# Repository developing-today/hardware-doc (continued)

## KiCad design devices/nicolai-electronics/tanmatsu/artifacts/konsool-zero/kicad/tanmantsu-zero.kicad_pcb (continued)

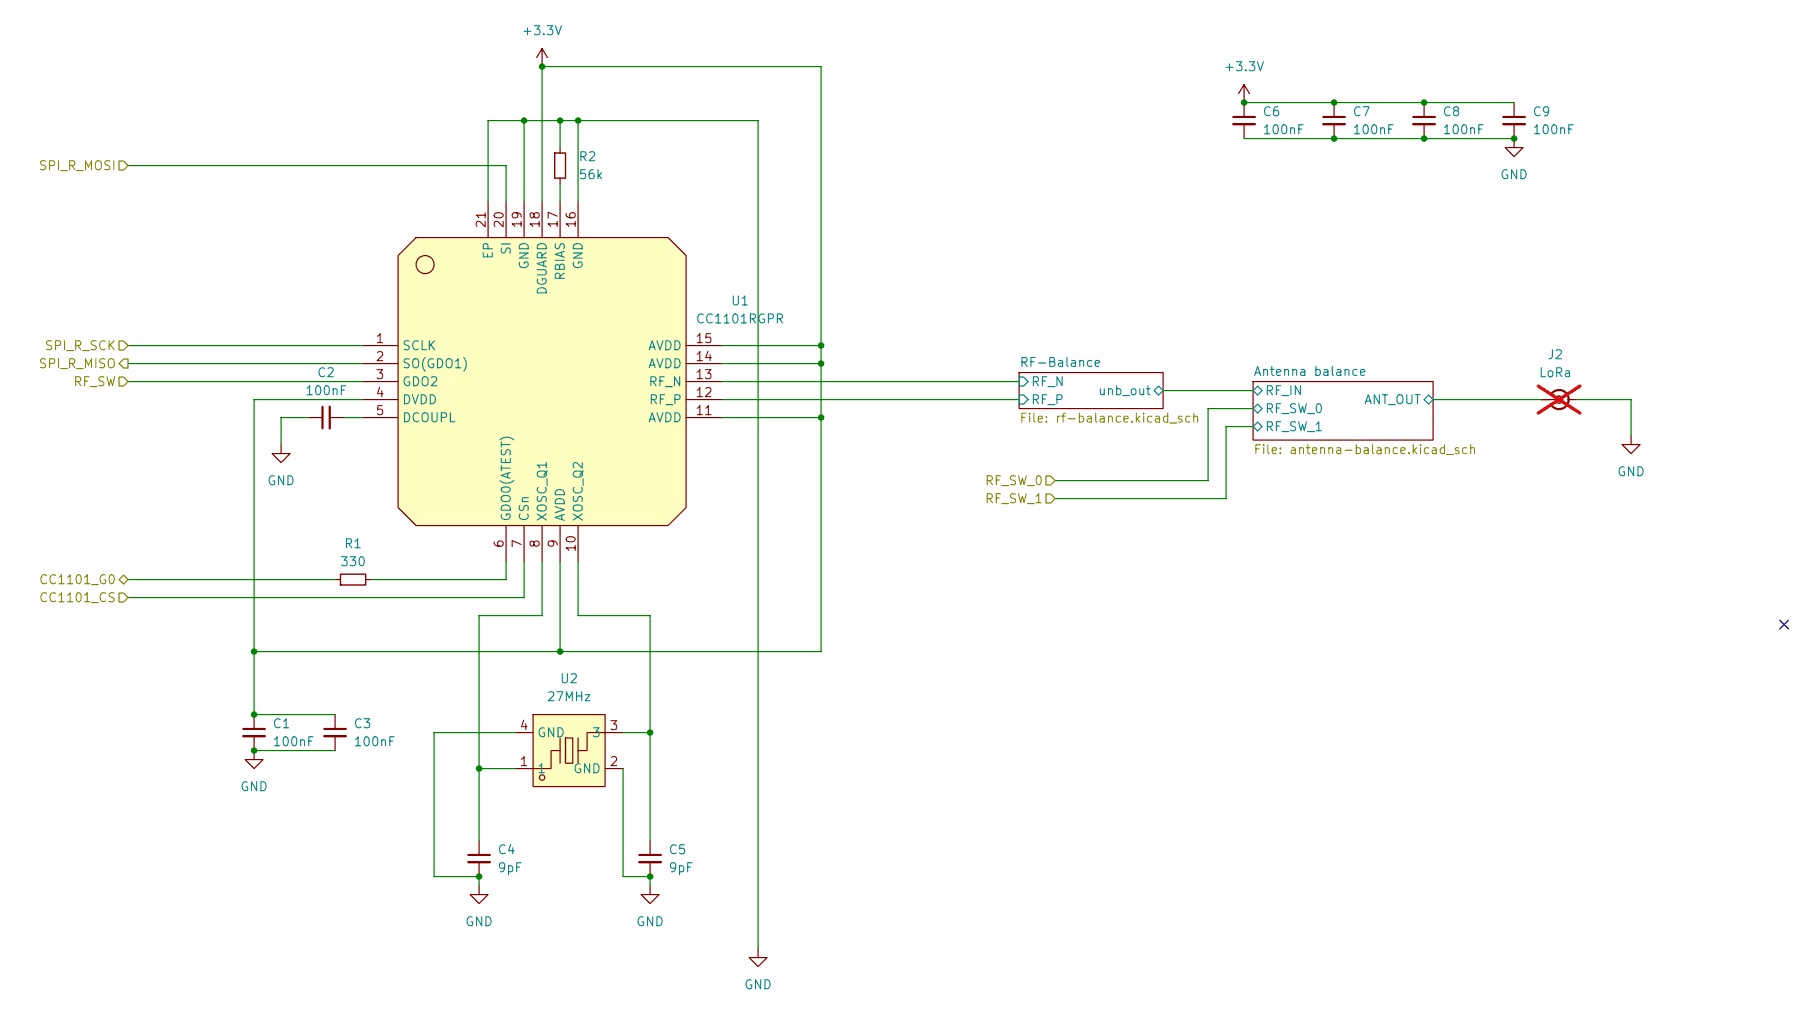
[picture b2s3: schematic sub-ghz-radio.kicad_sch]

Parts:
C1, C2, C3, C6, C7, C8, C9: 100nF; C_0402_1005Metric; LCSC C5448844
C4, C5: 9pF; C_0402_1005Metric; LCSC C426043
J2: LoRa; SMA_Samtec_SMA-J-P-H-ST-EM1_EdgeMount; not fitted
R1: 330; R_0402_1005Metric; LCSC C25104
R2: 56k; R_0402_1005Metric; LCSC C203188
U1: CC1101RGPR; QFN-20_L4.0-W4.0-P0.5-TL-EP; LCSC Part C29953
U2: 27MHz; OSC-SMD_4P-L3.2-W2.5-BL; LCSC Part C555573

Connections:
+3.3V: C1.1, C3.1, C6.1, C7.1, C8.1, C9.1, U1.4 (DVDD), U1.9 (AVDD), U1.11 (AVDD), U1.14 (AVDD), U1.15 (AVDD), U1.18 (DGUARD); also elsewhere on the board
/sub-GHz-radio/Antenna balance/ANT_OUT: J2.1 (In); also elsewhere on the board
/sub-GHz-radio/RF-Balance/RF_N: U1.13 (RF_N); also elsewhere on the board
/sub-GHz-radio/RF-Balance/RF_P: U1.12 (RF_P); also elsewhere on the board
E0: U1.3 (GDO2); also elsewhere on the board
E1: R1.1; also elsewhere on the board
GND: C1.2, C2.1, C3.2, C4.2, C5.2, C6.2, C7.2, C8.2, C9.2, J2.2 (Ext), R2.1, U1.16 (GND), U1.19 (GND), U1.21 (EP), U2.2 (GND), U2.4 (GND); also elsewhere on the board
unnamed: C2.2, U1.5 (DCOUPL)
unnamed: R1.2, U1.6 (GDO0(ATEST))
unnamed: R2.2, U1.17 (RBIAS)
unnamed: C4.1, U1.8 (XOSC_Q1), U2.1
unnamed: C5.1, U1.10 (XOSC_Q2), U2.3
SPI_CMD: U1.20 (SI); also elsewhere on the board
SPI_D0: U1.2 (SO(GDO1)); also elsewhere on the board
SPI_D3: U1.7 (CSn); also elsewhere on the board
SPI_SCK: U1.1 (SCLK); also elsewhere on the board

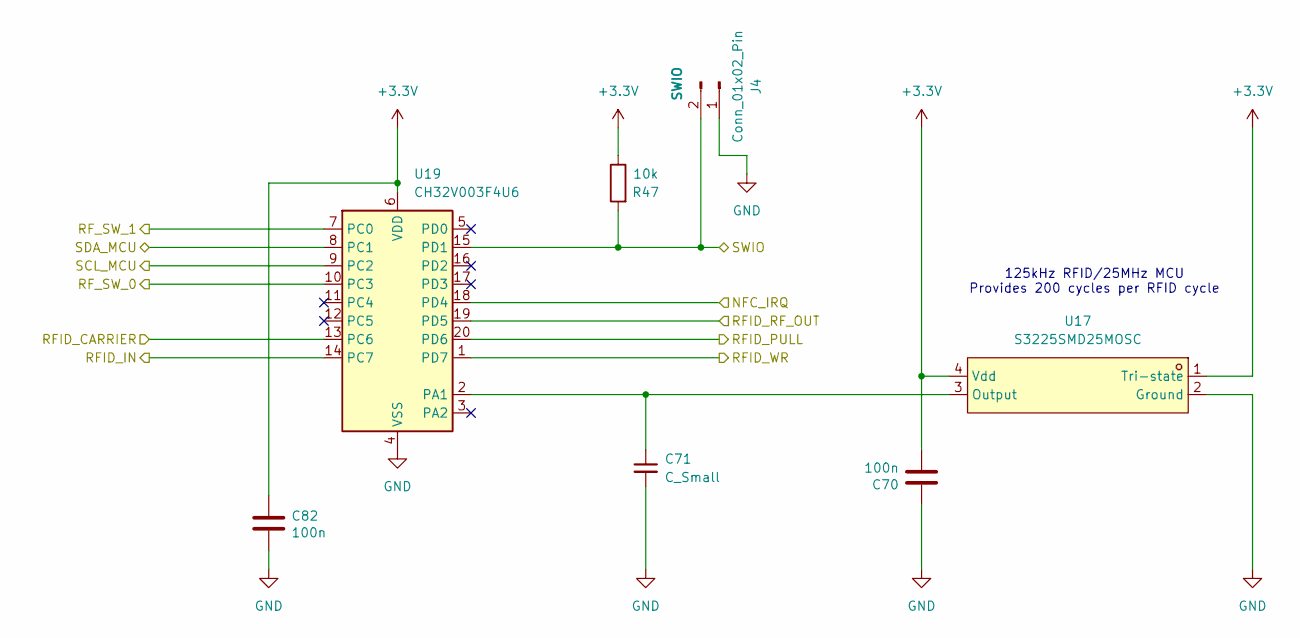
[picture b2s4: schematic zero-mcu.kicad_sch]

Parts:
C70, C82: 100n; C_0402_1005Metric; LCSC C307331
C71: C_Small; C_0402_1005Metric; LCSC C1548
J4: Conn_01x02_Pin; PinHeader_1x02_P2.54mm_Vertical
R47: 10k; R_0402_1005Metric; LCSC C60490
U17: S3225SMD25MOSC; OSC-SMD_4P-L3.2-W2.5-BL; LCSC Part C7431183
U19: CH32V003F4U6; QFN-20-1EP_3x3mm_P0.4mm_EP1.65x1.65mm

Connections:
+3.3V: C70.2, C82.1, R47.1, U17.1 (Tri-state), U17.4 (Vdd), U19.6 (VDD); also elsewhere on the board
E4: J4.2, R47.2, U19.15 (PD1); also elsewhere on the board
GND: C70.1, C71.2, C82.2, J4.1, U17.2 (Ground), U19.4 (VSS), U19.21 (VSS); also elsewhere on the board
INT_SCL: U19.9 (PC2); also elsewhere on the board
INT_SDA: U19.8 (PC1); also elsewhere on the board
NFC_IRQ: U19.18 (PD4); also elsewhere on the board
unnamed: C71.1, U17.3 (Output), U19.2 (PA1)
RFID_CARRIER: U19.13 (PC6); also elsewhere on the board
RFID_IN: U19.14 (PC7); also elsewhere on the board
RFID_PULL: U19.20 (PD6); also elsewhere on the board
RFID_RF_OUT: U19.19 (PD5); also elsewhere on the board
RFID_WR_IN: U19.1 (PD7); also elsewhere on the board
RF_SW_0: U19.10 (PC3); also elsewhere on the board
RF_SW_1: U19.7 (PC0); also elsewhere on the board

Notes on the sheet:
125kHz RFID/25MHz MCU Provides 200 cycles per RFID cycle

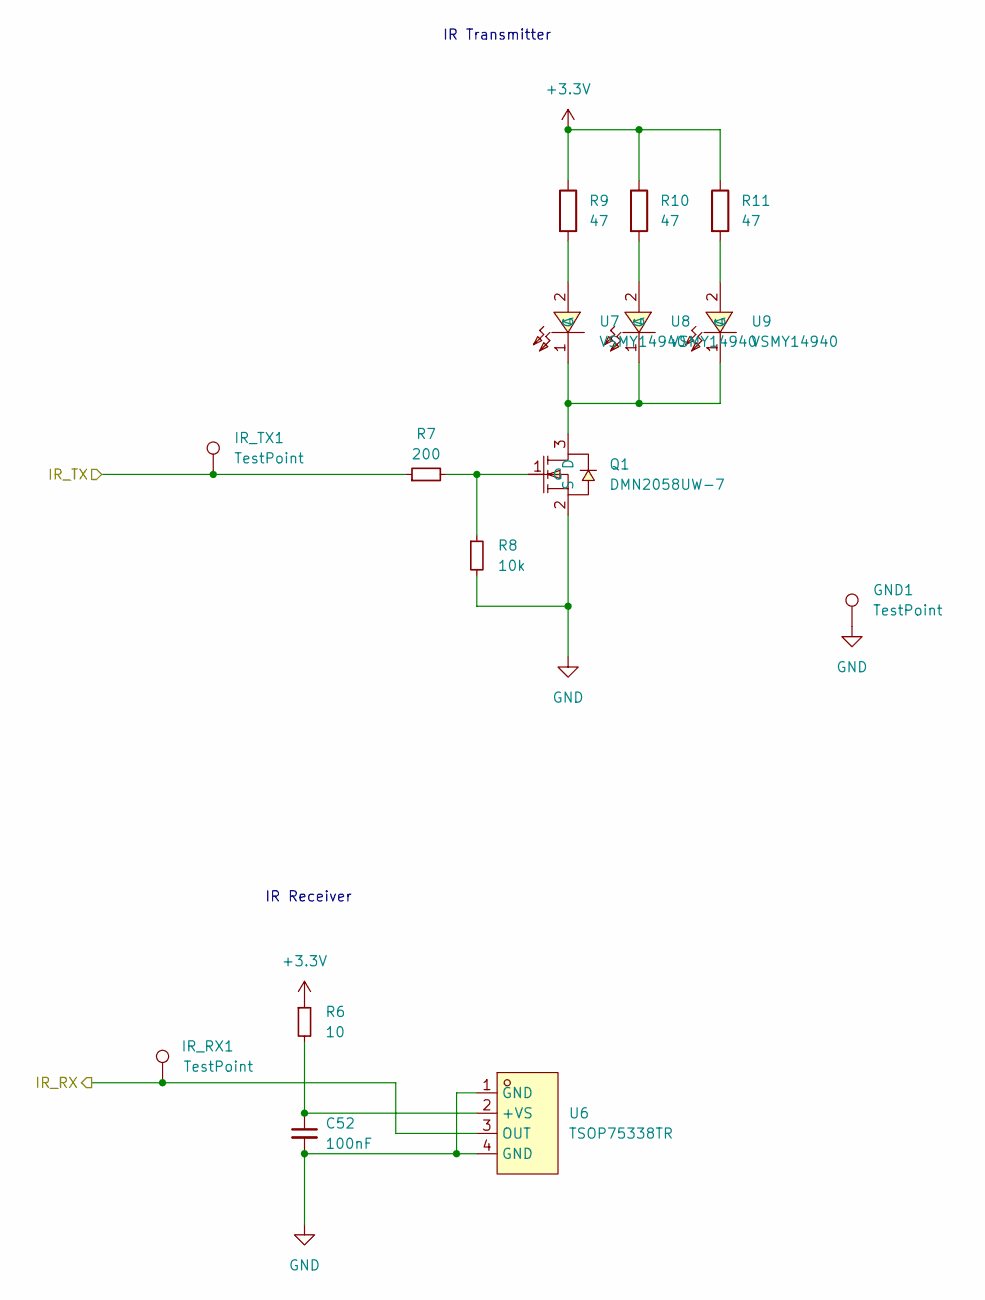
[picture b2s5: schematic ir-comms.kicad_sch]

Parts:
C52: 100nF; C_0402_1005Metric; LCSC C5448844
GND1: TestPoint; TestPoint_Pad_D1.0mm
IR_RX1: TestPoint; TestPoint_Pad_D1.0mm
IR_TX1: TestPoint; TestPoint_Pad_D1.0mm
Q1: DMN2058UW-7; SOT-323-3_L2.2-W1.3-P1.30-LS2.1-BR; LCSC Part C2760648
R6: 10; R_0402_1005Metric
R7: 200; R_0402_1005Metric; LCSC C25087
R8: 10k; R_0402_1005Metric; LCSC C25744
R9, R10, R11: 47; R_0805_2012Metric; LCSC C17714
U6: TSOP75338TR; SENSOR-SMD_TSOP75238TR; LCSC Part C6561231
U7, U8, U9: VSMY14940; LED-SMD_VSMY14940; LCSC Part C511069

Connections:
+3.3V: R6.1, R9.1, R10.1, R11.1; also elsewhere on the board
E9: IR_RX1.1, U6.3 (OUT); also elsewhere on the board
E10: IR_TX1.1, R7.1; also elsewhere on the board
GND: C52.2, GND1.1, Q1.2 (S), R8.2, U6.1 (GND), U6.4 (GND); also elsewhere on the board
unnamed: Q1.3 (D), U7.1 (C), U8.1 (C), U9.1 (C)
unnamed: Q1.1 (G), R7.2, R8.1
unnamed: C52.1, R6.2, U6.2 (+VS)
unnamed: R9.2, U7.2 (A)
unnamed: R10.2, U8.2 (A)
unnamed: R11.2, U9.2 (A)

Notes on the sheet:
IR Receiver
IR Transmitter

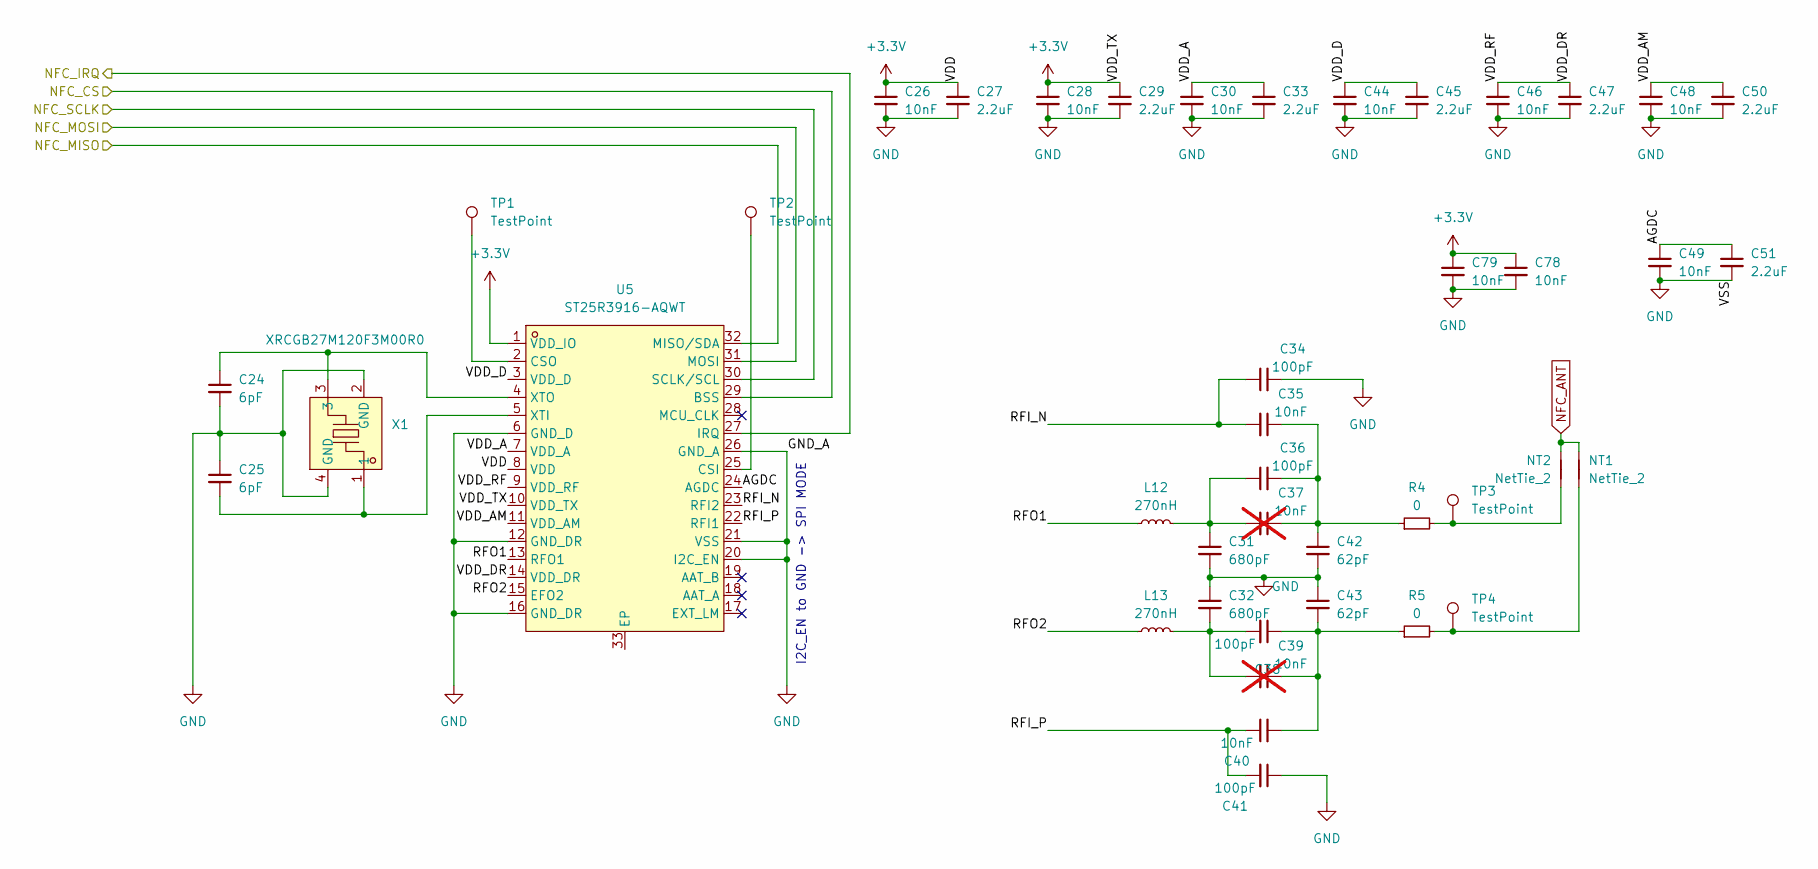
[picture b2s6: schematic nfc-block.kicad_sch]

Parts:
C24, C25: 6pF; C_0402_1005Metric; LCSC C1575
C26, C28, C30, C35, C40, C44, C46, C48, C49, C78, C79: 10nF; C_0402_1005Metric; LCSC C15195
C27, C29, C33, C45, C47, C50, C51: 2.2uF; C_0603_1608Metric; LCSC C23630
C31, C32: 680pF; C_0402_1005Metric; LCSC C295936
C34, C36, C38, C41: 100pF; C_0402_1005Metric; LCSC C1523
C37, C39: 10nF; C_0402_1005Metric; LCSC C15195; not fitted
C42, C43: 62pF; L_0402_1005Metric; LCSC C3887028
L12, L13: 270nH; L_0402_1005Metric; LCSC C76784
NT1, NT2: NetTie_2; NetTie-2_SMD_Pad0.5mm
R4, R5: 0; R_0402_1005Metric; LCSC C17168
TP1, TP2: TestPoint; TestPoint_Pad_1.0x1.0mm
TP3, TP4: TestPoint; TestPoint_Pad_D1.0mm
U5: ST25R3916-AQWT; VFQFPN-32_L5.0-W5.0-P0.50-TL-EP3.5; LCSC Part C2908147
X1: XRCGB27M120F3M00R0; CRYSTAL-SMD_4P-L2.0-W1.6-BL-B; LCSC Part C576558

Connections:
+3.3V: C26.1, C27.1, C28.1, C29.1, C78.1, C79.1, U5.1 (VDD_IO), U5.8 (VDD), U5.10 (VDD_TX); also elsewhere on the board
/NFC block/AGDC: C49.1, C51.1, U5.24 (AGDC)
/NFC block/RFI_N: C34.1, C35.2, U5.23 (RFI2)
/NFC block/RFI_P: C40.1, C41.2, U5.22 (RFI1)
/NFC block/RFO1: L12.1, U5.13 (RFO1)
/NFC block/RFO2: L13.1, U5.15 (EFO2)
/NFC block/VDD_A: C30.1, C33.1, U5.7 (VDD_A)
/NFC block/VDD_AM: C48.1, C50.1, U5.11 (VDD_AM)
/NFC block/VDD_D: C44.1, C45.1, U5.3 (VDD_D)
/NFC block/VDD_DR: C46.1, C47.1, U5.9 (VDD_RF), U5.14 (VDD_DR)
E3: U5.29 (BSS); also elsewhere on the board
GND: C24.2, C25.1, C26.2, C27.2, C28.2, C29.2, C30.2, C31.2, C32.1, C33.2, C34.2, C41.1, C42.2, C43.1, C44.2, C45.2, C46.2, C47.2, C48.2, C49.2, C50.2, C51.2, C78.2, C79.2, U5.6 (GND_D), U5.12 (GND_DR), U5.16 (GND_DR), U5.20 (I2C_EN), U5.21 (VSS), U5.26 (GND_A), X1.2 (GND), X1.4 (GND); also elsewhere on the board
NFC_ANT: NT1.2, NT2.1
NFC_IRQ: U5.27 (IRQ); also elsewhere on the board
unnamed: C31.1, C36.1, C37.2, L12.2
unnamed: C32.2, C38.2, C39.2, L13.2
unnamed: C35.1, C36.2, C37.1, C42.1, R4.1
unnamed: C38.1, C39.1, C40.2, C43.2, R5.1
unnamed: NT1.1, R5.2, TP4.1
unnamed: NT2.2, R4.2, TP3.1
unnamed: TP2.1, U5.25 (CSI)
unnamed: TP1.1, U5.2 (CSO)
unnamed: C25.2, U5.5 (XTI), X1.1
unnamed: C24.1, U5.4 (XTO), X1.3
SPI_CMD: U5.31 (MOSI); also elsewhere on the board
SPI_D0: U5.32 (MISO/SDA); also elsewhere on the board
SPI_SCK: U5.30 (SCLK/SCL); also elsewhere on the board

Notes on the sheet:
I2C_EN to GND -> SPI MODE

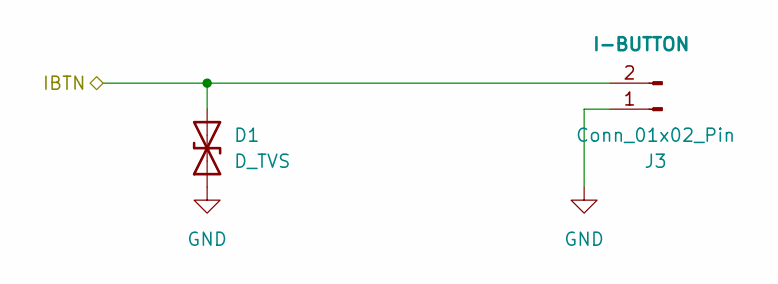
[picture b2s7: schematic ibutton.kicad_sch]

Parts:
D1: D_TVS; D_0402_1005Metric; LCSC C19626254
J3: Conn_01x02_Pin; PinHeader_1x02_P2.54mm_Vertical

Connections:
GND: D1.1 (A1), J3.1; also elsewhere on the board
IBTN: D1.2 (A2), J3.2

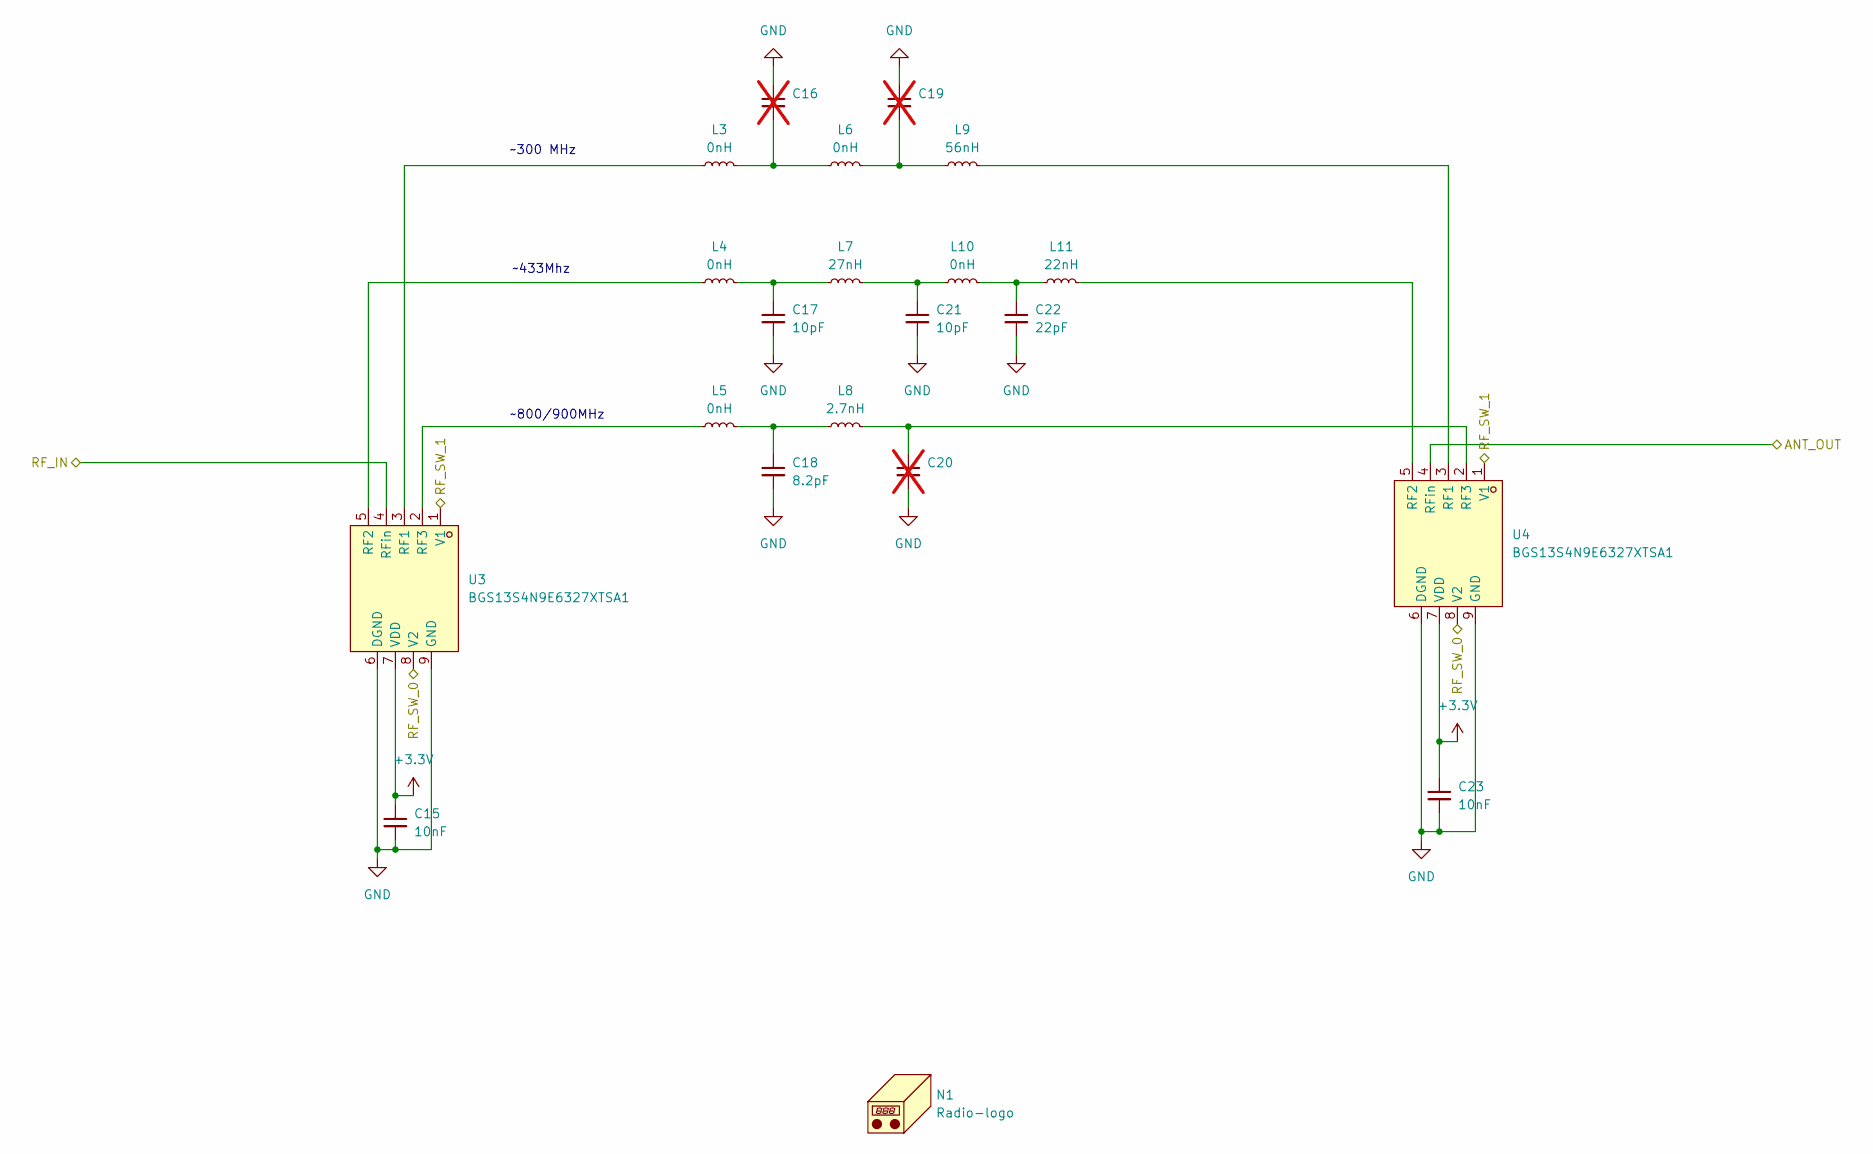
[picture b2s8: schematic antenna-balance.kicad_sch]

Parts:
C15, C23: 10nF; C_0402_1005Metric; LCSC C15195
C16, C19, C20: C_0402_1005Metric; LCSC C32949; not fitted
C17, C21: 10pF; C_0402_1005Metric; LCSC C32949
C18: 8.2pF; C_0402_1005Metric; LCSC C76984
C22: 22pF; C_0402_1005Metric; LCSC C1555
L3, L4, L5, L6, L10: 0nH; L_0402_1005Metric; LCSC C17168
L7: 27nH; L_0402_1005Metric; LCSC C98759
L8: 2.7nH; L_0402_1005Metric; LCSC C76770
L9: 56nH; L_0402_1005Metric; LCSC C76777
L11: 22nH; L_0402_1005Metric; LCSC C76768
N1: Radio-logo; radio-logo
U3, U4: BGS13S4N9E6327XTSA1; TSNP-9_L1.1-W1.1-P0.40-BL; LCSC Part C2151921

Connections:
+3.3V: C15.1, C23.1, U3.7 (VDD), U4.7 (VDD); also elsewhere on the board
/sub-GHz-radio/Antenna balance/ANT_OUT: U4.4 (RFin); also elsewhere on the board
/sub-GHz-radio/Antenna balance/RF_IN: U3.4 (RFin); also elsewhere on the board
GND: C15.2, C16.1, C17.2, C18.2, C19.1, C20.2, C21.2, C22.2, C23.2, U3.6 (DGND), U3.9 (GND), U4.6 (DGND), U4.9 (GND); also elsewhere on the board
unnamed: C16.2, L3.2, L6.1
unnamed: C17.1, L4.2, L7.1
unnamed: C18.1, L5.2, L8.1
unnamed: C19.2, L6.2, L9.1
unnamed: C21.1, L7.2, L10.1
unnamed: C22.1, L10.2, L11.1
unnamed: L3.1, U3.3 (RF1)
unnamed: L4.1, U3.5 (RF2)
unnamed: L5.1, U3.2 (RF3)
unnamed: L9.2, U4.3 (RF1)
unnamed: L11.2, U4.5 (RF2)
unnamed: C20.1, L8.2, U4.2 (RF3)
RF_SW_0: U3.1 (V1), U4.1 (V1); also elsewhere on the board
RF_SW_1: U3.8 (V2), U4.8 (V2); also elsewhere on the board

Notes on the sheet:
~800/900MHz
~300 MHz
~433Mhz

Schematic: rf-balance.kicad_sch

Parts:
C10: 0.6pF; C_0402_1005Metric; LCSC C2857968
C11, C12: 100pF; C_0402_1005Metric; LCSC C1546
C13: ??; C_0402_1005Metric; not fitted
C14: 1.2pF; C_0402_1005Metric; LCSC C72135
L1: 3.3nH; IND-SMD_L1.0-W0.5; LCSC Part C2981735
L2: LQG15HS6N8J02D; L0402-RD; LCSC Part C77110
R3: 0; R_0402_1005Metric; LCSC C17168
T1: B0310J50100AHF; XFMR-SMD_6P-L2.1-W1.3-P0.65-BL; LCSC Part C502721

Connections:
/sub-GHz-radio/Antenna balance/RF_IN: R3.2; also elsewhere on the board
/sub-GHz-radio/RF-Balance/RF_N: C10.1, C11.1; also elsewhere on the board
/sub-GHz-radio/RF-Balance/RF_P: C10.2, C12.1; also elsewhere on the board
GND: C13.2, C14.2, T1.2 (GND); also elsewhere on the board
unnamed: C11.2, T1.3 (Balanced)
unnamed: C12.2, T1.4 (Balanced)
unnamed: C13.1, L1.2, L2.1
unnamed: C14.1, L2.2, R3.1
unnamed: L1.1, T1.1 (Unbalanced)

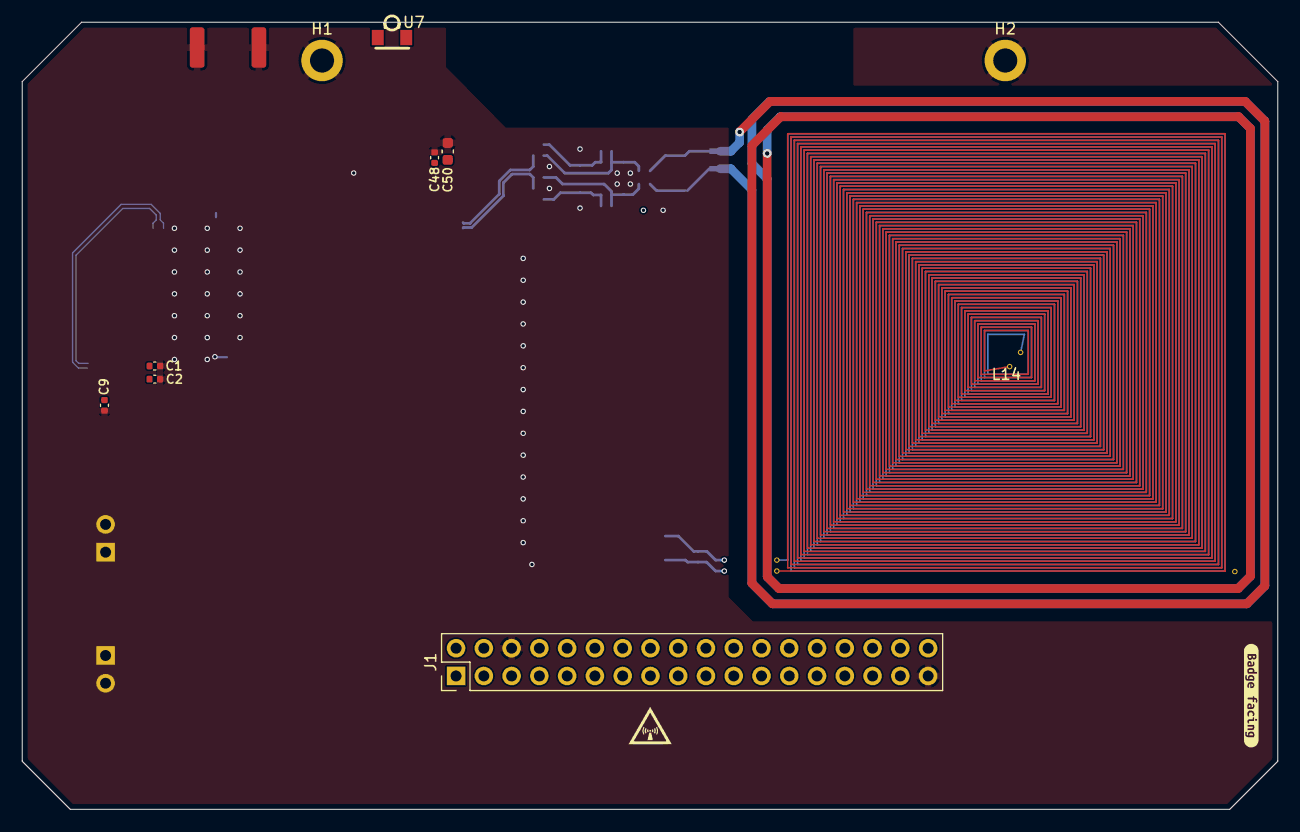
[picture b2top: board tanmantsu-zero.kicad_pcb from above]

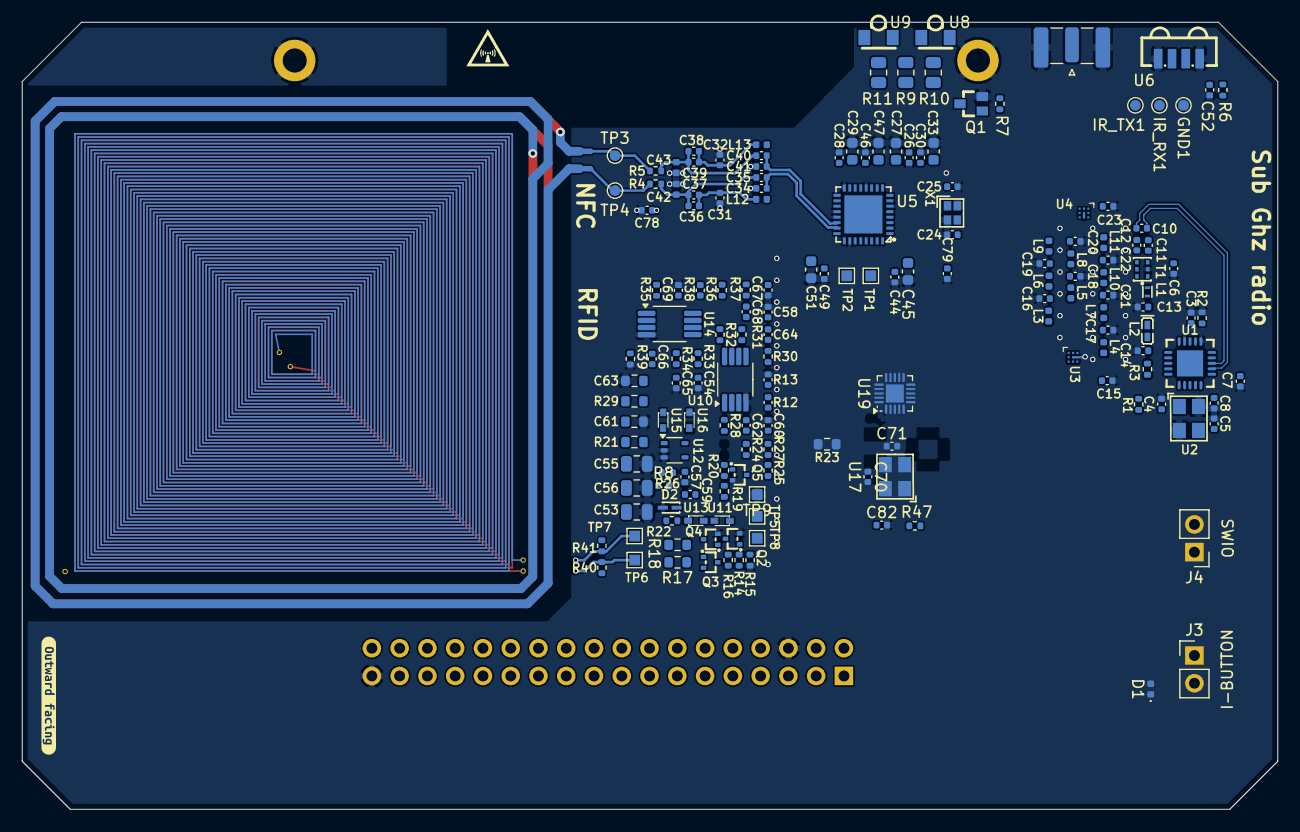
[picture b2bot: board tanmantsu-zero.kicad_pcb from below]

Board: 4 copper layers, 114.8 x 72.0 mm, 182 parts (169 on the bottom side), 105 nets.

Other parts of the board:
N1#2: Radio-logo; radio-logo
kibuzzard-672F417C: G***; kibuzzard-672F417C
kibuzzard-672F4776: G***; kibuzzard-672F4776
